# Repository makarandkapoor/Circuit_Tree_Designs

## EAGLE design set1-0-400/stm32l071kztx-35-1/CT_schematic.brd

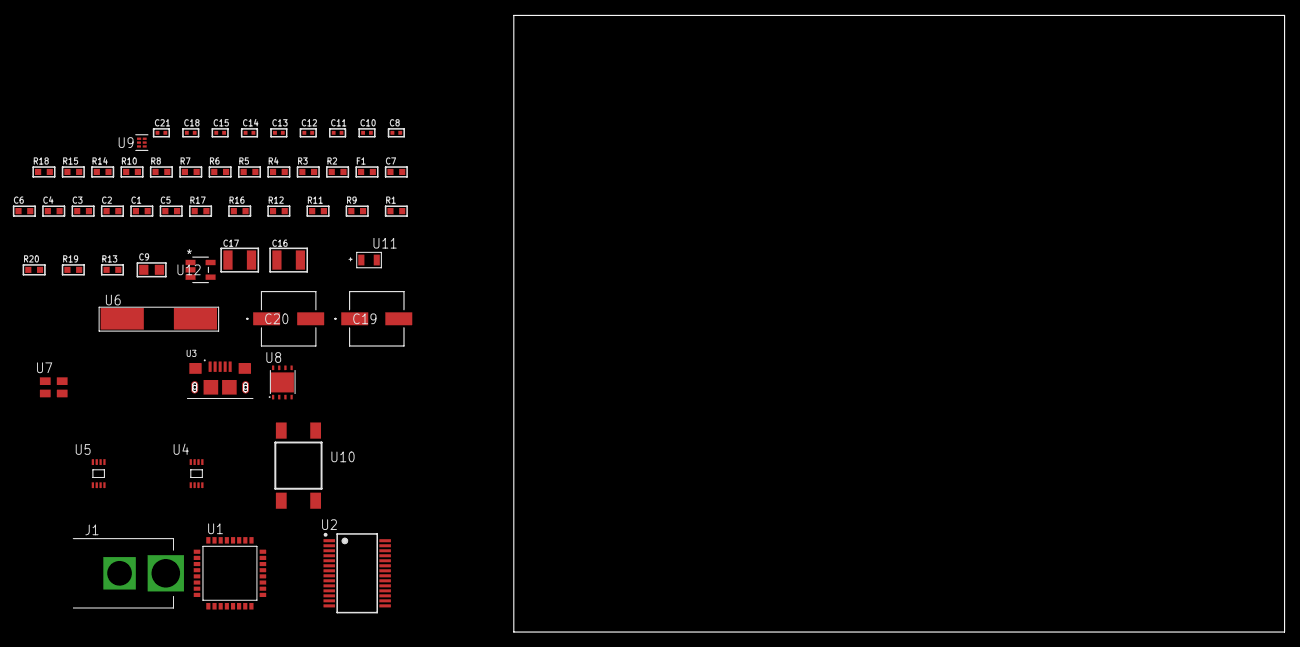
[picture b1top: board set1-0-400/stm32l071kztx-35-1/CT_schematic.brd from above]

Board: 2 copper layers, 55 parts (0 on the bottom side), 32 nets, no tracks yet.

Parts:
C1, C2, C3, C4: 1e-07; C0603
C5: 4.7e-06; C0603
C6: 1e-08; C0603
C7: 1e-06; C0603
C8, C10, C11, C18: 1e-07; C0402
C9: 4.7e-06; C0805
C12, C13, C14, C15, C21: 1e-08; C0402
C16, C17: 1e-05; C1210
C19, C20: 0.0001; EXV-9H
F1: 240.0; L0603
J1: PJ-037B; PJ-037B_PACKAGE
R1, R9, R11, R12, R16, R17: 10000.0; R0603
R2, R15: 1000.0; R0603
R3: 1600.5; R0603
R4, R10: 4700.0; R0603
R5, R6, R7, R8: 2200.0; R0603
R13: 100000.0; R0603
R14: 2231.0; R0603
R18: 9100.0; R0603
R19: 680000.0; R0603
R20: 120000.0; R0603
U1: STM32L071KZT6; LQFP32
U2: FT232RL-REEL; SSOP-28
U3: 10118193-0001LF; FCI_10118193-0001LF
U4, U5: 24AA16-I/MC; TDFN-8/6MM
U6: ABLS-12.000MHZ-B4-T
U7: ASEK-32.768KHz-ECST; ASEK
U8: LP3878SDX-ADJ/NOPB; WSON-8
U9: TPS3895ADRYR; SON-6
U10: 4-1437565-2; SW_4-1437565-2
U11: Q65110A2395; LGM67K-G1J2-24-Z
U12: nc7sz125m5x; NC7SZ125M5X

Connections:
CLK_CRYSTAL_U2_27: U2.27, U6.1
CLK_CRYSTAL_U2_28: U2.28, U6.2
CLK_U1_2: U1.2, U7.3
GND: C1.2, C2.2, C3.2, C4.2, C5.2, C6.2, C7.2, C8.2, C9.2, C10.2, C11.2, C12.2, C13.2, C14.2, C15.2, C16.2, C17.2, C18.2, C19.2, C20.2, C21.2, J1.2, R2.2, R9.2, R12.2, R15.2, R18.2, R20.2, U1.16, U1.32, U2.7, U2.18, U2.21, U2.25, U2.26, U3.5, U3.6, U3.7, U3.8, U3.9, U4.4, U4.7, U5.4, U7.2, U8.3, U8.PAD, U9.2, U11.C, U12.1, U12.3
NET_U1_4: R4.1, U1.4, U12.4
NET_U1_5: C6.1, C7.1, F1.1, U1.5
NET_U1_18: R7.1, U1.18, U5.6
NET_U1_19: R5.1, U1.19, U4.6
NET_U1_20: R6.1, U1.20, U4.5
NET_U1_27: R8.1, U1.27, U5.5
NET_U1_29: R3.1, U1.29, U11.A
NET_U1_30: R1.1, U1.30, U10.3, U10.4
NET_U1_31: R9.1, U1.31
NET_U2_14: R11.1, U2.14
NET_U2_17: C10.1, U2.17
NET_U2_19: R12.1, U2.19
NET_U3_1: R10.1, U3.1
NET_U3_2: U2.16, U3.2
NET_U3_3: U2.15, U3.3
NET_U8_1: C15.1, U8.1
NET_U8_6: R14.2, R15.1, U8.6
NET_U8_8: R13.1, U8.8
NET_U9_1: R17.1, R18.1, U9.1
NET_U9_3: R19.2, R20.1, U9.3
NET_U9_4: R16.1, U9.4, U12.2
NET_U10_1: R2.1, U10.1, U10.2
PROC_LPUART1_CTS: U1.12, U2.3
PROC_LPUART1_RTS: U1.15, U2.11
PROC_LPUART1_RX: U1.9, U2.1
PROC_LPUART1_TX: U1.8, U2.5
VCC_S1_15V9: C16.1, C19.1, C20.1, J1.1, R13.2, U8.4
VCC_TIER1_3V3: C1.1, C2.1, C3.1, C4.1, C5.1, C8.1, C9.1, C11.1, C12.1, C13.1, C14.1, C17.1, C18.1, C21.1, F1.2, R1.2, R3.2, R4.2, R5.2, R6.2, R7.2, R8.2, R11.2, R14.1, R16.2, R17.2, R19.1, U1.1, U1.17, U2.4, U2.20, U4.8, U5.7, U5.8, U7.4, U8.5, U9.6, U12.5

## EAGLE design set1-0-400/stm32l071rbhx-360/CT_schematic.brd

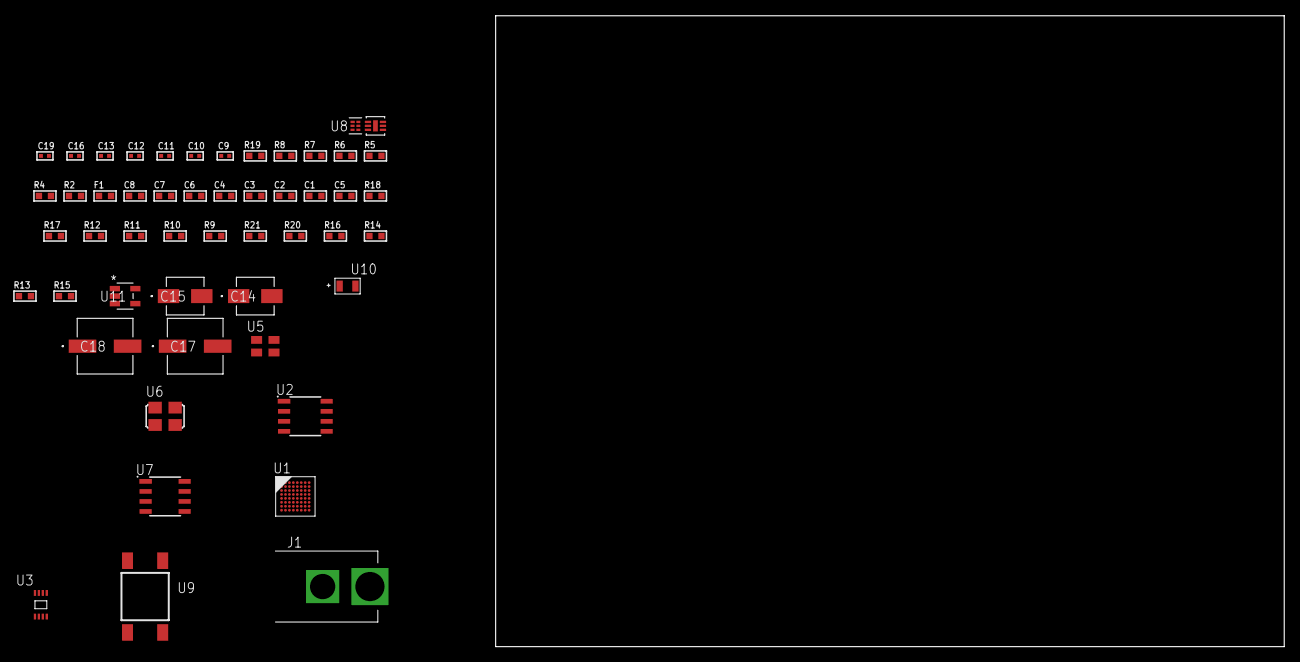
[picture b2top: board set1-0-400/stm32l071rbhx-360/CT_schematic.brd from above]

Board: 2 copper layers, 100.0 x 80.0 mm, 51 parts (0 on the bottom side), 26 nets, no tracks yet.

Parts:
C1, C2, C3, C4, C6: 1e-07; C0603
C5: 4.7e-06; C0603
C7: 1e-08; C0603
C8: 1e-06; C0603
C9, C10, C12, C13, C19: 1e-08; C0402
C11, C16: 1e-07; C0402
C14: 1e-06; EXV-9B
C15: 2.2e-06; EXV-9B
C17, C18: 0.0001; EXV-9H
F1: 240.0; L0603
J1: PJ-037B; PJ-037B_PACKAGE
R2: 1000.0; R0603
R4: 4700.0; R0603
R5, R6, R7, R8: 2200.0; R0603
R9, R10, R11, R12, R17, R18: 10000.0; R0603
R13, R14, R16: 100000.0; R0603
R15: 164658.62; R0603
R19: 9100.0; R0603
R20: 680000.0; R0603
R21: 120000.0; R0603
U1: STM32L071RBH6; TFBGA64
U2: AT25128B-SSHL-T; SOIC-8
U3: 24AA04-I/MC; TDFN-8/6MM
U4: SI7006-A20-IM; DFN-6
U5: ASEK-32.768KHz-ECST; ASEK
U6: ASFL1-25MHZ-NCS; ASFL1
U7: LP2954AIMX/NOPB; LP2954
U8: TPS3895ADRYR; SON-6
U9: 4-1437565-2; SW_4-1437565-2
U10: Q65110A2395; LGM67K-G1J2-24-Z
U11: nc7sz125m5x; NC7SZ125M5X

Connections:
CLK_U1_A1: U1.A1, U5.3
CLK_U1_C1: U1.C1, U6.3
GND: C1.2, C2.2, C3.2, C4.2, C5.2, C6.2, C7.2, C8.2, C9.2, C10.2, C11.2, C12.2, C13.2, C14.2, C15.2, C16.2, C17.2, C18.2, C19.2, J1.2, R2.2, R9.2, R16.2, R19.2, R21.2, U1.C2, U1.D4, U1.D5, U1.D6, U1.F1, U2.4, U3.4, U4.2, U4.7, U5.2, U6.2, U7.4, U8.2, U10.C, U11.1, U11.3
NET_U1_A3: R6.1, U1.A3, U4.1
NET_U1_B3: R5.1, U1.B3, U4.6
NET_U1_B4: R9.1, U1.B4
NET_U1_E1: R4.1, U1.E1, U11.4
NET_U1_F8: R8.1, U1.F8, U3.5
NET_U1_G7: R7.1, U1.G7, U3.6
NET_U1_H1: C7.1, C8.1, F1.1, U1.G1, U1.H1
NET_U1_H8: U9.3, U9.4
NET_U2_3: R10.1, U2.3
NET_U2_7: R12.1, U2.7
NET_U7_3: R14.1, U7.3
NET_U7_5: R13.1, U7.5
NET_U7_7: R15.2, R16.1, U7.7
NET_U8_1: R18.1, R19.1, U8.1
NET_U8_3: R20.2, R21.1, U8.3
NET_U8_4: R17.1, U8.4, U11.2
NET_U9_1: R2.1, U9.1, U9.2
PROC_SPI1_MISO: U1.A4, U2.2
PROC_SPI1_MOSI: U1.B8, U2.5
PROC_SPI1_NSS: R11.1, U1.A6, U2.1
PROC_SPI1_SCK: U1.A5, U2.6
VCC_S1_16V8: C14.1, C17.1, C18.1, J1.1, R14.2, U7.8
VCC_TIER1_3V3: C1.1, C2.1, C3.1, C4.1, C5.1, C6.1, C9.1, C10.1, C11.1, C12.1, C13.1, C15.1, C16.1, C19.1, F1.2, R4.2, R5.2, R6.2, R7.2, R8.2, R10.2, R11.2, R12.2, R13.2, R15.1, R17.2, R18.2, R20.1, U1.B2, U1.D2, U1.E4, U1.E5, U1.E6, U2.8, U3.7, U3.8, U4.5, U5.4, U6.4, U7.1, U8.6, U11.5

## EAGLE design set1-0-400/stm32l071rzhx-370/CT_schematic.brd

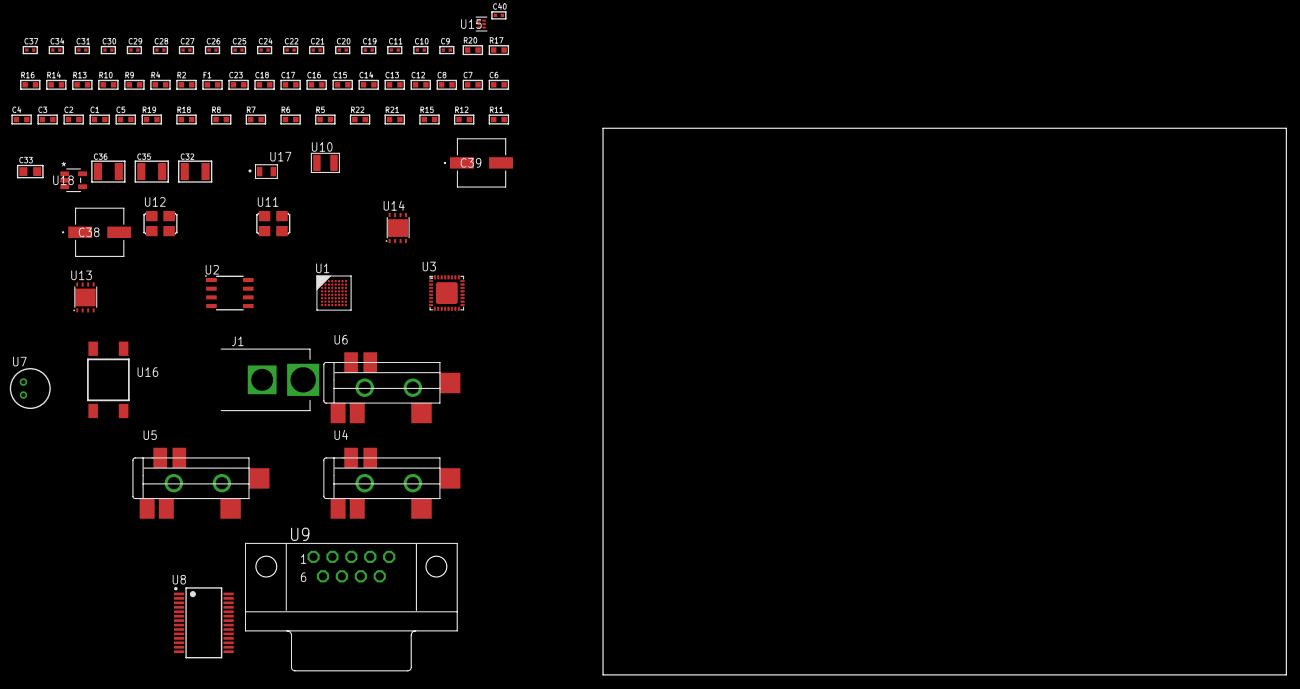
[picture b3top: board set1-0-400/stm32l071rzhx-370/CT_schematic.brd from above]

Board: 2 copper layers, 100.0 x 80.0 mm, 80 parts (0 on the bottom side), 59 nets, no tracks yet.

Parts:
C1, C2, C3, C4, C6: 1e-07; C0603
C5: 4.7e-06; C0603
C7: 1e-08; C0603
C8, C12, C13, C14, C15, C16, C17, C18, C23: 1e-06; C0603
C9, C10: 1e-11; C0402
C11, C29, C30, C31, C34, C40: 1e-08; C0402
C19, C20, C21, C22, C24, C25, C26, C27, C28, C37: 1e-07; C0402
C32, C35, C36: 1e-05; C1210
C33: 1e-05; C0805
C38, C39: 0.0001; EXV-9H
F1: 240.0; L0603
J1: PJ-037B; PJ-037B_PACKAGE
R2, R14, R17: 1000.0; R0603
R4: 4700.0; R0603
R5, R6, R7, R8, R18, R19: 10000.0; R0603
R9, R10: 1270.0; R0603
R11, R12, R15: 100000.0; R0603
R13: 200.0; R0603
R16: 2231.0; R0603
R20: 9100.0; R0603
R21: 680000.0; R0603
R22: 120000.0; R0603
U1: STM32L071RZH6; TFBGA64
U2: AT25M01-SSHM-T; SOIC-8
U3: SGTL5000XNAA3; QFN-32
U4, U5, U6: SJ-43515TS-SMT-TR
U7: WM-64PCT; WM-64PC
U8: ST3241EBPR; SSOP-28
U9: 182-009-113R531; 182-009-MALE
U10: ABS07-32.768KHZ-7-T
U11: ASFL-24.57MHZ-NCS; ASFL1
U12: ASFL1-25MHZ-NCS; ASFL1
U13, U14: LP3878SDX-ADJ/NOPB; WSON-8
U15: TPS3895ADRYR; SON-6
U16: 4-1437565-2; SW_4-1437565-2
U17: Q65110A2395; LGM67K-G1J2-24-Z
U18: nc7sz125m5x; NC7SZ125M5X

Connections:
CLK_CRYSTAL_U1_A1: C9.1, U1.A1, U10.1
CLK_CRYSTAL_U1_B1: C10.1, U1.B1, U10.2
CLK_U1_C1: U1.C1, U12.3
CLK_U3_21: U3.21, U11.3
GND: C1.2, C2.2, C3.2, C4.2, C5.2, C6.2, C7.2, C8.2, C9.2, C10.2, C11.2, C19.2, C20.2, C21.2, C22.2, C23.2, C24.2, C27.2, C28.2, C29.2, C30.2, C31.2, C32.2, C33.2, C34.2, C35.2, C36.2, C37.2, C38.2, C39.2, C40.2, J1.2, R2.2, R5.2, R10.2, R14.2, R17.2, R20.2, R22.2, U1.C2, U1.D4, U1.D5, U1.D6, U1.F1, U2.4, U3.1, U3.3, U3.7, U3.EXP, U5.1, U6.1, U7.2, U8.23, U8.25, U9.5, U11.2, U12.2, U13.3, U13.PAD, U14.3, U14.PAD, U15.2, U17.C, U18.1, U18.3
NET_U1_B4: R5.1, U1.B4
NET_U1_E1: R4.1, U1.E1, U18.4
NET_U1_H1: C7.1, C8.1, F1.1, U1.G1, U1.H1
NET_U1_H8: U16.3, U16.4
NET_U2_3: R6.1, U2.3
NET_U2_7: R8.1, U2.7
NET_U3_10: C22.1, U3.10
NET_U3_29: R9.1, U3.29
NET_U3_31: R10.1, U3.31
NET_U4_1: U3.4, U4.1
NET_U4_2: U3.2, U4.2
NET_U4_5: U3.6, U4.5
NET_U5_2: C13.1, U5.2
NET_U5_5: C12.1, U5.5
NET_U6_2: C15.1, C16.1, U6.2
NET_U6_5: C14.1, U6.5
NET_U6_13: C15.2, C16.2
NET_U7_1: C17.1, C18.1, C23.1, U3.16, U7.1
NET_U7_15: C17.2, C18.2
NET_U8_1: C26.1, U8.1
NET_U8_2: C26.2, U8.2
NET_U8_3: C28.1, U8.3
NET_U8_22: R11.1, U8.22
NET_U8_24: C25.2, U8.24
NET_U8_27: C27.1, U8.27
NET_U8_28: C25.1, U8.28
NET_U9_2: U8.4, U9.2
NET_U9_3: U8.9, U9.3
NET_U9_7: U8.5, U9.7
NET_U9_8: U8.10, U9.8
NET_U13_1: C31.1, U13.1
NET_U13_6: R13.2, R14.1, U13.6
NET_U13_8: R12.1, U13.8
NET_U14_1: C34.1, U14.1
NET_U14_6: R16.2, R17.1, U14.6
NET_U14_8: R15.1, U14.8
NET_U15_1: R19.1, R20.1, U15.1
NET_U15_3: R21.2, R22.1, U15.3
NET_U15_4: R18.1, U15.4, U18.2
NET_U16_1: R2.1, U16.1, U16.2
PROC_I2S2_CK: U1.G8, U3.24
PROC_I2S2_SD: U1.F7, U3.26
PROC_I2S2_WS: U1.A3, U3.23
PROC_LPUART1_CTS: U1.G4, U8.13
PROC_LPUART1_RTS: U1.B5, U8.18
PROC_LPUART1_RX: U1.A8, U8.19
PROC_LPUART1_TX: U1.A7, U8.14
PROC_SPI1_MISO: U1.A4, U2.2
PROC_SPI1_MOSI: U1.B8, U2.5
PROC_SPI1_NSS: R7.1, U1.A6, U2.1
PROC_SPI1_SCK: U1.A5, U2.6
VCC_S1_15V1: C32.1, C35.1, C38.1, C39.1, J1.1, R12.2, R15.2, U13.4, U14.4
VCC_TIER1_1V2: C19.1, C33.1, R13.1, U3.30, U13.5
VCC_TIER1_3V3: C1.1, C2.1, C3.1, C4.1, C5.1, C6.1, C11.1, C20.1, C21.1, C24.1, C29.1, C30.1, C36.1, C37.1, C40.1, F1.2, R4.2, R6.2, R7.2, R8.2, R9.2, R11.2, R16.1, R18.2, R19.2, R21.1, U1.B2, U1.D2, U1.E4, U1.E5, U1.E6, U2.8, U3.5, U3.20, U8.26, U11.4, U12.4, U14.5, U15.6, U18.5

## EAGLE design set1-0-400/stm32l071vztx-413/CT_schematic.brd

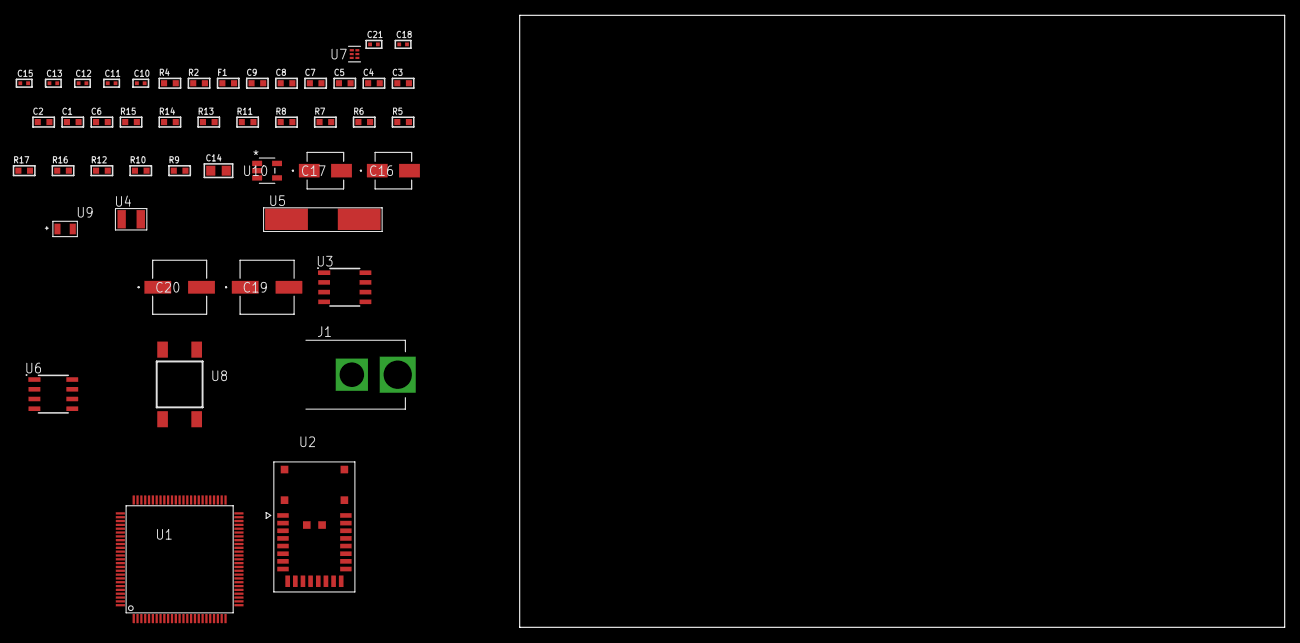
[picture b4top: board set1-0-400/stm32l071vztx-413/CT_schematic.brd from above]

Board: 2 copper layers, 100.0 x 80.0 mm, 48 parts (0 on the bottom side), 28 nets, no tracks yet.

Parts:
C1, C2, C3, C4, C5, C7: 1e-07; C0603
C6: 4.7e-06; C0603
C8: 1e-08; C0603
C9: 1e-06; C0603
C10, C11, C12, C13: 1e-11; C0402
C14: 1e-05; C0805
C15, C21: 1e-08; C0402
C16: 1e-06; EXV-9B
C17: 2.2e-06; EXV-9B
C18: 1e-07; C0402
C19, C20: 0.0001; EXV-9H
F1: 240.0; L0603
J1: PJ-037B; PJ-037B_PACKAGE
R2: 1000.0; R0603
R4: 4700.0; R0603
R5, R6, R7, R8, R13, R14: 10000.0; R0603
R9, R10, R12: 100000.0; R0603
R11: 47000.0; R0603
R15: 82000.0; R0603
R16: 300000.0; R0603
R17: 120000.0; R0603
U1: STM32L071VZT6; LQFP100
U2: A2500R24A00GM
U3: AT25512N-SH-T; SOIC-8
U4: ABS07-32.768KHZ-7-T
U5: ABLS-25.000MHZ-B2F-T
U6: LP2954AIMX/NOPB; LP2954
U7: TPS3895ADRYR; SON-6
U8: 4-1437565-2; SW_4-1437565-2
U9: Q65110A2395; LGM67K-G1J2-24-Z
U10: nc7sz125m5x; NC7SZ125M5X

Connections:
CLK_CRYSTAL_U1_8: C10.1, U1.8, U4.1
CLK_CRYSTAL_U1_9: C11.1, U1.9, U4.2
CLK_CRYSTAL_U1_12: C12.1, U1.12, U5.1
CLK_CRYSTAL_U1_13: C13.1, U1.13, U5.2
GND: C1.2, C2.2, C3.2, C4.2, C5.2, C6.2, C7.2, C8.2, C9.2, C10.2, C11.2, C12.2, C13.2, C14.2, C15.2, C16.2, C17.2, C18.2, C19.2, C20.2, C21.2, J1.2, R2.2, R5.2, R12.2, R15.2, R17.2, U1.19, U1.20, U1.27, U1.49, U1.74, U1.99, U2.8, U2.17, U3.4, U6.4, U7.2, U9.C, U10.1, U10.3
NET_U1_14: R4.1, U1.14, U10.4
NET_U1_22: C8.1, C9.1, F1.1, U1.21, U1.22
NET_U1_94: R5.1, U1.94
NET_U1_98: U8.3, U8.4
NET_U3_3: R6.1, U3.3
NET_U3_7: R8.1, U3.7
NET_U6_3: R10.1, U6.3
NET_U6_5: R9.1, U6.5
NET_U6_7: R11.2, R12.1, U6.7
NET_U7_1: R14.1, R15.1, U7.1
NET_U7_3: R16.2, R17.1, U7.3
NET_U7_4: R13.1, U7.4, U10.2
NET_U8_1: R2.1, U8.1, U8.2
PROC_SPI1_MISO: U1.31, U2.10
PROC_SPI1_MOSI: U1.32, U2.11
PROC_SPI1_NSS: U1.29, U2.12
PROC_SPI1_SCK: U1.30, U2.9
PROC_SPI2_MISO: U1.17, U3.2
PROC_SPI2_MOSI: U1.18, U3.5
PROC_SPI2_NSS: R7.1, U1.51, U3.1
PROC_SPI2_SCK: U1.47, U3.6
VCC_S1_8V2: C16.1, C19.1, C20.1, J1.1, R10.2, U6.8
VCC_TIER1_1V8: C1.1, C2.1, C3.1, C4.1, C5.1, C6.1, C7.1, C14.1, C15.1, C17.1, C18.1, C21.1, F1.2, R4.2, R6.2, R7.2, R8.2, R9.2, R11.1, R13.2, R14.2, R16.1, U1.6, U1.28, U1.50, U1.73, U1.75, U1.100, U2.18, U3.8, U6.1, U7.6, U10.5

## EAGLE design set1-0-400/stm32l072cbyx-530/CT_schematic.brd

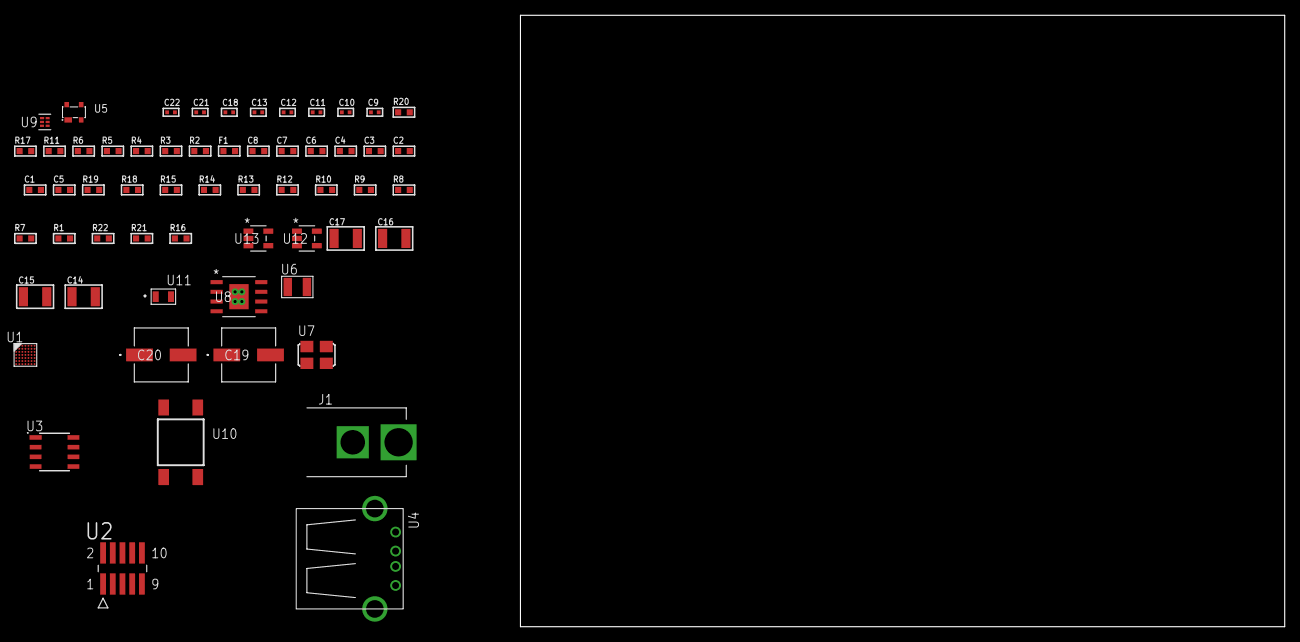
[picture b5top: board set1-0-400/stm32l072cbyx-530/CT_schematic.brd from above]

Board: 2 copper layers, 100.0 x 80.0 mm, 59 parts (0 on the bottom side), 29 nets, no tracks yet.

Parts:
C1, C2, C3, C4, C8: 1e-07; C0603
C5: 4.7e-06; C0603
C6: 1e-08; C0603
C7: 1e-06; C0603
C9, C10: 1e-11; C0402
C11, C18: 1e-07; C0402
C12, C13, C21, C22: 1e-08; C0402
C14, C15, C16, C17: 1e-05; C1210
C19, C20: 0.0001; EXV-9H
F1: 240.0; L0603
J1: PJ-037B; PJ-037B_PACKAGE
R1, R7, R8, R9, R10, R12, R13, R14, R15, R18, R19: 10000.0; R0603
R2: 1000.0; R0603
R3: 1600.5; R0603
R4: 4700.0; R0603
R5, R6, R17: 2200.0; R0603
R11: 5.0; R0603
R16: 4031.5447154472; R0603
R20: 9100.0; R0603
R21: 680000.0; R0603
R22: 120000.0; R0603
U1: STM32L072CBY6; WLCSP49
U2: FTSH-105-01-L-DV-K; SAMTEC_FTSH-105-01-L-DV-K
U3: AT24C02D-SSHM-T; AT24C02D
U4: 61400416021; USB-A-H
U5: prtr5v0u2ax; SOT143B
U6: ABS07-32.768KHZ-7-T
U7: ASFL1-25MHZ-NCS; ASFL1
U8: MIC5234YME; SOIC-8_EP
U9: TPS3895ADRYR; SON-6
U10: 4-1437565-2; SW_4-1437565-2
U11: Q65110A2395; LGM67K-G1J2-24-Z
U12, U13: nc7sz125m5x; NC7SZ125M5X

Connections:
CLK_CRYSTAL_U1_C6: C9.1, U1.C6, U6.1
CLK_CRYSTAL_U1_C7: C10.1, U1.C7, U6.2
CLK_U1_D6: U1.D6, U7.3
GND: C1.2, C2.2, C3.2, C4.2, C5.2, C6.2, C7.2, C8.2, C9.2, C10.2, C11.2, C12.2, C13.2, C14.2, C15.2, C16.2, C17.2, C18.2, C19.2, C20.2, C21.2, C22.2, J1.2, R2.2, R7.2, R11.2, R12.2, R14.2, R15.2, R17.2, R20.2, R22.2, U1.D4, U2.3, U2.5, U3.4, U4.4, U4.5, U4.6, U5.1, U7.2, U8.7, U8.EPAD, U9.2, U11.C, U12.2, U12.3, U13.1, U13.3
NET_U1_A5: R7.1, U1.A5
NET_U1_A6: R6.1, U1.A6, U3.5
NET_U1_B4: R5.1, U1.B4, U3.6
NET_U1_D5: R4.1, U1.D5, U13.4
NET_U1_F7: C6.1, C7.1, F1.1, U1.E6, U1.F7
NET_U1_G6: R3.1, U1.G6, U11.A
NET_U1_G7: R1.1, U1.G7, U10.3, U10.4
NET_U2_9: R11.1, U2.9
NET_U3_1: R13.1, U3.1
NET_U3_2: R14.1, U3.2
NET_U3_3: R15.1, U3.3
NET_U3_7: R12.1, U3.7
NET_U5_4: U4.1, U5.4
NET_U8_4: R16.2, R17.1, U8.4
NET_U9_1: R19.1, R20.1, U9.1
NET_U9_3: R21.2, R22.1, U9.3
NET_U9_4: R18.1, U9.4, U12.4, U13.2
NET_U10_1: R2.1, U10.1, U10.2
PROC_SYS_SWCLK: R9.1, U1.B2, U2.4
PROC_SYS_SWDIO: R10.1, U1.C2, U2.2
PROC_USB_DM: U1.D2, U4.2, U5.3
PROC_USB_DP: U1.B1, U4.3, U5.2
RST_OUT_U2_JTAG_RST_B: R8.1, U2.10, U12.1
VCC_S1_5V1: C14.1, C15.1, C19.1, C20.1, J1.1, U8.5, U8.8
VCC_TIER1_3V3: C1.1, C2.1, C3.1, C4.1, C5.1, C8.1, C11.1, C12.1, C13.1, C16.1, C17.1, C18.1, C21.1, C22.1, F1.2, R1.2, R3.2, R4.2, R5.2, R6.2, R8.2, R9.2, R10.2, R13.2, R16.1, R18.2, R19.2, R21.1, U1.A1, U1.A7, U1.B6, U1.G2, U2.1, U3.8, U7.4, U8.1, U9.6, U12.5, U13.5

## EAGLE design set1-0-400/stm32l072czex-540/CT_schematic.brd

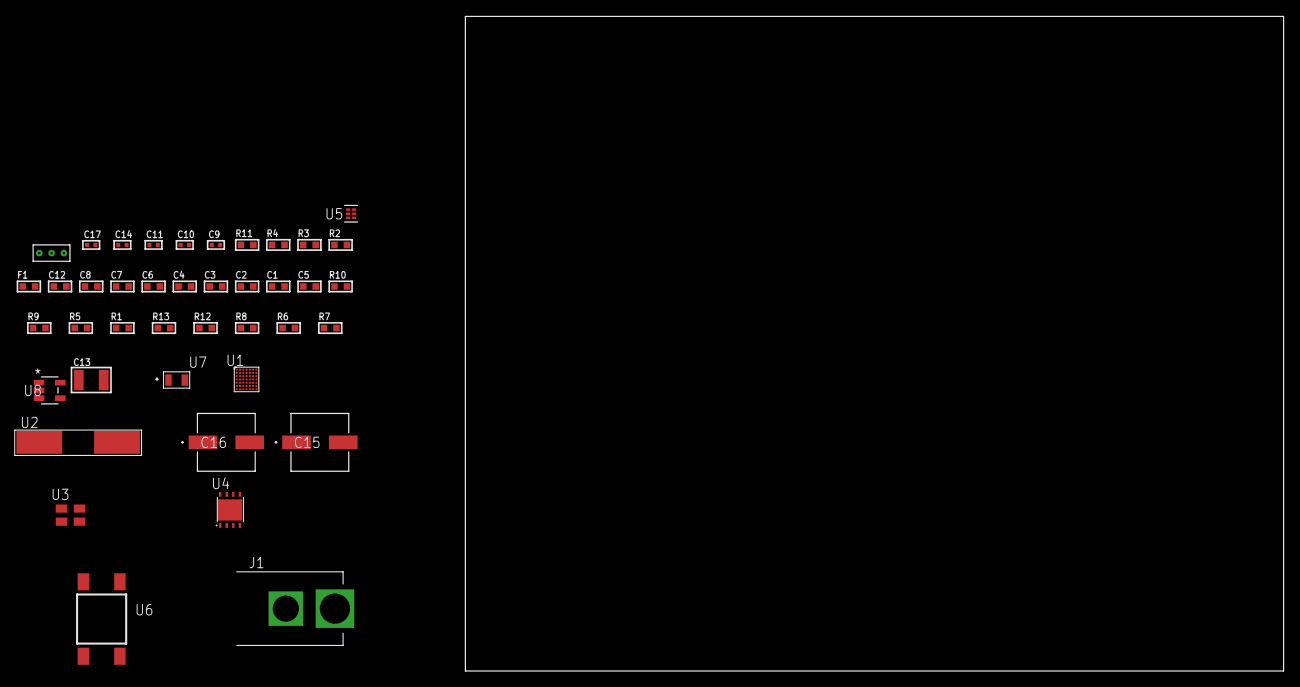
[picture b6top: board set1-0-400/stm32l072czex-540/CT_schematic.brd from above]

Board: 2 copper layers, 100.0 x 80.0 mm, 41 parts (0 on the bottom side), 19 nets, no tracks yet.

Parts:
C1, C2, C3, C4, C8: 1e-07; C0603
C5: 4.7e-06; C0603
C6: 1e-08; C0603
C7: 1e-06; C0603
C9, C10: 1e-11; C0402
C11, C17: 1e-08; C0402
C12: 8e-07; R0603
C13: 1e-05; C1210
C14: 1e-07; C0402
C15, C16: 0.0001; EXV-9H
F1: 240.0; L0603
J1: PJ-037B; PJ-037B_PACKAGE
R1, R5, R9, R10: 10000.0; R0603
R2: 1000.0; R0603
R3: 1600.5; R0603
R4: 4700.0; R0603
R6, R8: 100000.0; R0603
R7: 153694.38; R0603
R11: 9100.0; R0603
R12: 680000.0; R0603
R13: 120000.0; R0603
U1: STM32L072CZE6TR; EWLCSP49
U2: ABLS-25.000MHZ-B2F-T
U3: ASEK-32.768KHz-ECST; ASEK
U4: LP2951ACSDX/NOPB; WSON-8
U5: TPS3895ADRYR; SON-6
U6: 4-1437565-2; SW_4-1437565-2
U7: Q65110A2395; LGM67K-G1J2-24-Z
U8: nc7sz125m5x; NC7SZ125M5X
U9: Dummy; DUMMY_PACKAGE_81

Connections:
CLK_CRYSTAL_U1_D6: C9.1, U1.D6, U2.1
CLK_CRYSTAL_U1_D7: C10.1, U1.D7, U2.2
CLK_U1_C6: U1.C6, U3.3
GND: C1.2, C2.2, C3.2, C4.2, C5.2, C6.2, C7.2, C8.2, C9.2, C10.2, C11.2, C12.2, C13.2, C14.2, C15.2, C16.2, C17.2, J1.2, R2.2, R5.2, R8.2, R11.2, R13.2, U1.D4, U3.2, U4.3, U4.4, U4.PAD, U5.2, U7.C, U8.1, U8.3, U9.1
NET_U1_A5: R5.1, U1.A5
NET_U1_D5: R4.1, U1.D5, U8.4
NET_U1_F7: C6.1, C7.1, F1.1, U1.E6, U1.F7
NET_U1_G6: R3.1, U1.G6, U7.A
NET_U1_G7: R1.1, U1.G7, U6.3, U6.4
NET_U4_5: R6.1, U4.5
NET_U4_7: R7.2, R8.1, U4.7
NET_U5_1: R10.1, R11.1, U5.1
NET_U5_3: R12.2, R13.1, U5.3
NET_U5_4: R9.1, U5.4, U8.2
NET_U6_1: R2.1, U6.1, U6.2
PROC_PA15: U1.A2, U9.2
PROC_PB3: U1.A3, U9.3
VCC_S1_15V7: C12.1, C15.1, C16.1, J1.1, U4.8
VCC_TIER1_3V3: C1.1, C2.1, C3.1, C4.1, C5.1, C8.1, C11.1, C13.1, C14.1, C17.1, F1.2, R1.2, R3.2, R4.2, R6.2, R7.1, R9.2, R10.2, R12.1, U1.A1, U1.A7, U1.B6, U1.G2, U3.4, U4.1, U5.6, U8.5

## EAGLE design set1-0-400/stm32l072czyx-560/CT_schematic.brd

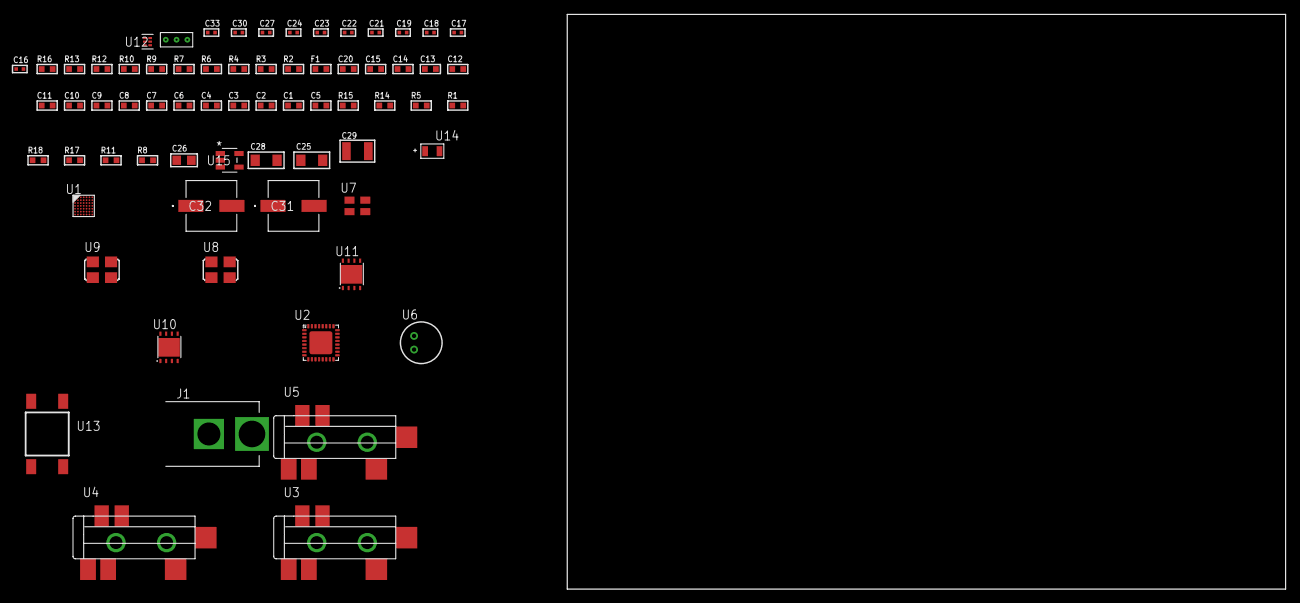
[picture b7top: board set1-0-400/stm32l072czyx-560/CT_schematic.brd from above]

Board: 2 copper layers, 100.0 x 80.0 mm, 69 parts (0 on the bottom side), 40 nets, no tracks yet.

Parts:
C1, C2, C3, C4, C8: 1e-07; C0603
C5: 4.7e-06; C0603
C6: 1e-08; C0603
C7, C9, C10, C11, C12, C13, C14, C15, C20: 1e-06; C0603
C16, C17, C18, C19, C30: 1e-07; C0402
C21, C22, C23, C24, C27, C33: 1e-08; C0402
C25, C28: 1e-05; C1206
C26: 1e-05; C0805
C29: 1e-05; C1210
C31, C32: 0.0001; EXV-9H
F1: 240.0; L0603
J1: PJ-037B; PJ-037B_PACKAGE
R1, R5, R14, R15: 10000.0; R0603
R2, R10, R13: 1000.0; R0603
R3: 1600.5; R0603
R4: 4700.0; R0603
R6, R7: 1270.0; R0603
R8, R11: 100000.0; R0603
R9: 200.0; R0603
R12: 2231.0; R0603
R16: 9100.0; R0603
R17: 680000.0; R0603
R18: 120000.0; R0603
U1: STM32L072CZY6; WLCSP49
U2: SGTL5000XNAA3; QFN-32
U3, U4, U5: SJ-43515TS-SMT-TR
U6: WM-64PCT; WM-64PC
U7: ASEK-32.768KHz-ECST; ASEK
U8: ASFL-24.57MHZ-NCS; ASFL1
U9: ASFL1-25MHZ-NCS; ASFL1
U10, U11: LP3878SDX-ADJ/NOPB; WSON-8
U12: TPS3895ADRYR; SON-6
U13: 4-1437565-2; SW_4-1437565-2
U14: Q65110A2395; LGM67K-G1J2-24-Z
U15: nc7sz125m5x; NC7SZ125M5X
U16: Dummy; DUMMY_PACKAGE_137

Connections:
CLK_U1_C6: U1.C6, U7.3
CLK_U1_D6: U1.D6, U9.3
CLK_U2_21: U2.21, U8.3
GND: C1.2, C2.2, C3.2, C4.2, C5.2, C6.2, C7.2, C8.2, C16.2, C17.2, C18.2, C19.2, C20.2, C21.2, C22.2, C23.2, C24.2, C25.2, C26.2, C27.2, C28.2, C29.2, C30.2, C31.2, C32.2, C33.2, J1.2, R2.2, R5.2, R7.2, R10.2, R13.2, R16.2, R18.2, U1.D4, U2.1, U2.3, U2.7, U2.EXP, U4.1, U5.1, U6.2, U7.2, U8.2, U9.2, U10.3, U10.PAD, U11.3, U11.PAD, U12.2, U14.C, U15.1, U15.3, U16.1
NET_U1_A5: R5.1, U1.A5
NET_U1_D5: R4.1, U1.D5, U15.4
NET_U1_F7: C6.1, C7.1, F1.1, U1.E6, U1.F7
NET_U1_G6: R3.1, U1.G6, U14.A
NET_U1_G7: R1.1, U1.G7, U13.3, U13.4
NET_U2_10: C19.1, U2.10
NET_U2_29: R6.1, U2.29
NET_U2_31: R7.1, U2.31
NET_U3_1: U2.4, U3.1
NET_U3_2: U2.2, U3.2
NET_U3_5: U2.6, U3.5
NET_U4_2: C10.1, U4.2
NET_U4_5: C9.1, U4.5
NET_U5_2: C12.1, C13.1, U5.2
NET_U5_5: C11.1, U5.5
NET_U5_13: C12.2, C13.2
NET_U6_1: C14.1, C15.1, C20.1, U2.16, U6.1
NET_U6_15: C14.2, C15.2
NET_U10_1: C24.1, U10.1
NET_U10_6: R9.2, R10.1, U10.6
NET_U10_8: R8.1, U10.8
NET_U11_1: C27.1, U11.1
NET_U11_6: R12.2, R13.1, U11.6
NET_U11_8: R11.1, U11.8
NET_U12_1: R15.1, R16.1, U12.1
NET_U12_3: R17.2, R18.1, U12.3
NET_U12_4: R14.1, U12.4, U15.2
NET_U13_1: R2.1, U13.1, U13.2
PROC_I2S2_CK: U1.F2, U2.24
PROC_I2S2_SD: U1.E1, U2.26
PROC_I2S2_WS: U1.A6, U2.23
PROC_PA15: U1.A2, U16.2
PROC_PB3: U1.A3, U16.3
VCC_S1_9V1: C25.1, C28.1, C31.1, C32.1, J1.1, R8.2, R11.2, U10.4, U11.4
VCC_TIER1_1V2: C16.1, C26.1, R9.1, U2.30, U10.5
VCC_TIER1_3V3: C1.1, C2.1, C3.1, C4.1, C5.1, C8.1, C17.1, C18.1, C21.1, C22.1, C23.1, C29.1, C30.1, C33.1, F1.2, R1.2, R3.2, R4.2, R6.2, R12.1, R14.2, R15.2, R17.1, U1.A1, U1.A7, U1.B6, U1.G2, U2.5, U2.20, U7.4, U8.4, U9.4, U11.5, U12.6, U15.5

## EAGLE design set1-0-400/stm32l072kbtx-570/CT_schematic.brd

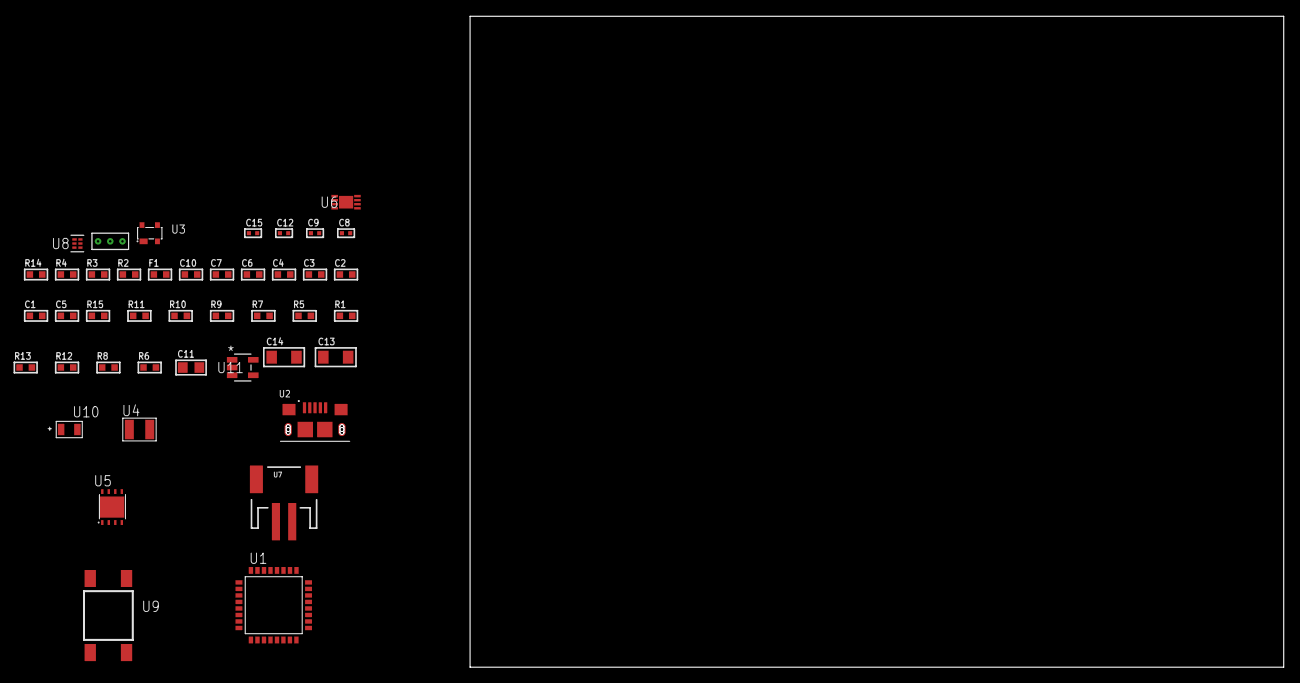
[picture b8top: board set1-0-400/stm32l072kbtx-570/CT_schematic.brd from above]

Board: 2 copper layers, 122.6 x 80.0 mm, 43 parts (0 on the bottom side), 23 nets, no tracks yet.

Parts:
C1, C2, C3, C4: 1e-07; C0603
C5: 4.7e-06; C0603
C6: 1e-08; C0603
C7, C10: 1e-06; C0603
C8, C9: 1e-11; C0402
C11: 1e-05; C0805
C12: 1e-07; C0402
C13, C14: 1e-05; C1206
C15: 1e-08; C0402
F1: 240.0; L0603
R1, R5, R9, R10, R15: 10000.0; R0603
R2: 1000.0; R0603
R3: 910.0; R0603
R4: 4700.0; R0603
R6, R8: 100000.0; R0603
R7: 36000.0; R0603
R11: 82000.0; R0603
R12: 300000.0; R0603
R13: 120000.0; R0603
R14: 2000.0; R0603
U1: STM32L072KBT6; LQFP32
U2: 10118193-0001LF; FCI_10118193-0001LF
U3: prtr5v0u2ax; SOT143B
U4: ABS07-32.768KHZ-7-T
U5: LP2951ACSDX/NOPB; WSON-8
U6: MCP73831T-2ACI/MC; DFN8_2X3MC
U7: S2B-PH-SM4-TB(LF)(SN); JST-2-SMD
U8: TPS3895ADRYR; SON-6
U9: 4-1437565-2; SW_4-1437565-2
U10: Q65110A2395; LGM67K-G1J2-24-Z
U11: nc7sz125m5x; NC7SZ125M5X
U12: Dummy; DUMMY_PACKAGE_90

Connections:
CLK_CRYSTAL_U1_2: C8.1, U1.2, U4.1
CLK_CRYSTAL_U1_3: C9.1, U1.3, U4.2
GND: C1.2, C2.2, C3.2, C4.2, C5.2, C6.2, C7.2, C8.2, C9.2, C10.2, C11.2, C12.2, C13.2, C14.2, C15.2, R2.2, R5.2, R8.2, R11.2, R13.2, R14.2, U1.16, U1.32, U2.5, U2.6, U2.7, U2.8, U2.9, U3.1, U5.3, U5.4, U5.PAD, U6.6, U6.9, U7.2, U8.2, U10.C, U11.1, U11.3, U12.1
INPUT_USBPOWER_5V: C13.1, R15.2, U2.1, U3.4, U6.1, U6.2
NET_U1_4: R4.1, U1.4, U11.4
NET_U1_5: C6.1, C7.1, F1.1, U1.5
NET_U1_29: R3.1, U1.29, U10.A
NET_U1_30: R1.1, U1.30, U9.3, U9.4
NET_U1_31: R5.1, U1.31
NET_U5_5: R6.1, U5.5
NET_U5_7: R7.2, R8.1, U5.7
NET_U6_5: R15.1, U6.5
NET_U6_8: R14.1, U6.8
NET_U8_1: R10.1, R11.1, U8.1
NET_U8_3: R12.2, R13.1, U8.3
NET_U8_4: R9.1, U8.4, U11.2
NET_U9_1: R2.1, U9.1, U9.2
PROC_PA0: U1.6, U12.2
PROC_PA1: U1.7, U12.3
PROC_USB_DM: U1.21, U2.2, U3.3
PROC_USB_DP: U1.22, U2.3, U3.2
VCC_S1_3V7: C10.1, C14.1, U5.8, U6.3, U6.4, U7.1
VCC_TIER1_1V8: C1.1, C2.1, C3.1, C4.1, C5.1, C11.1, C12.1, C15.1, F1.2, R1.2, R3.2, R4.2, R6.2, R7.1, R9.2, R10.2, R12.1, U1.1, U1.17, U5.1, U8.6, U11.5
